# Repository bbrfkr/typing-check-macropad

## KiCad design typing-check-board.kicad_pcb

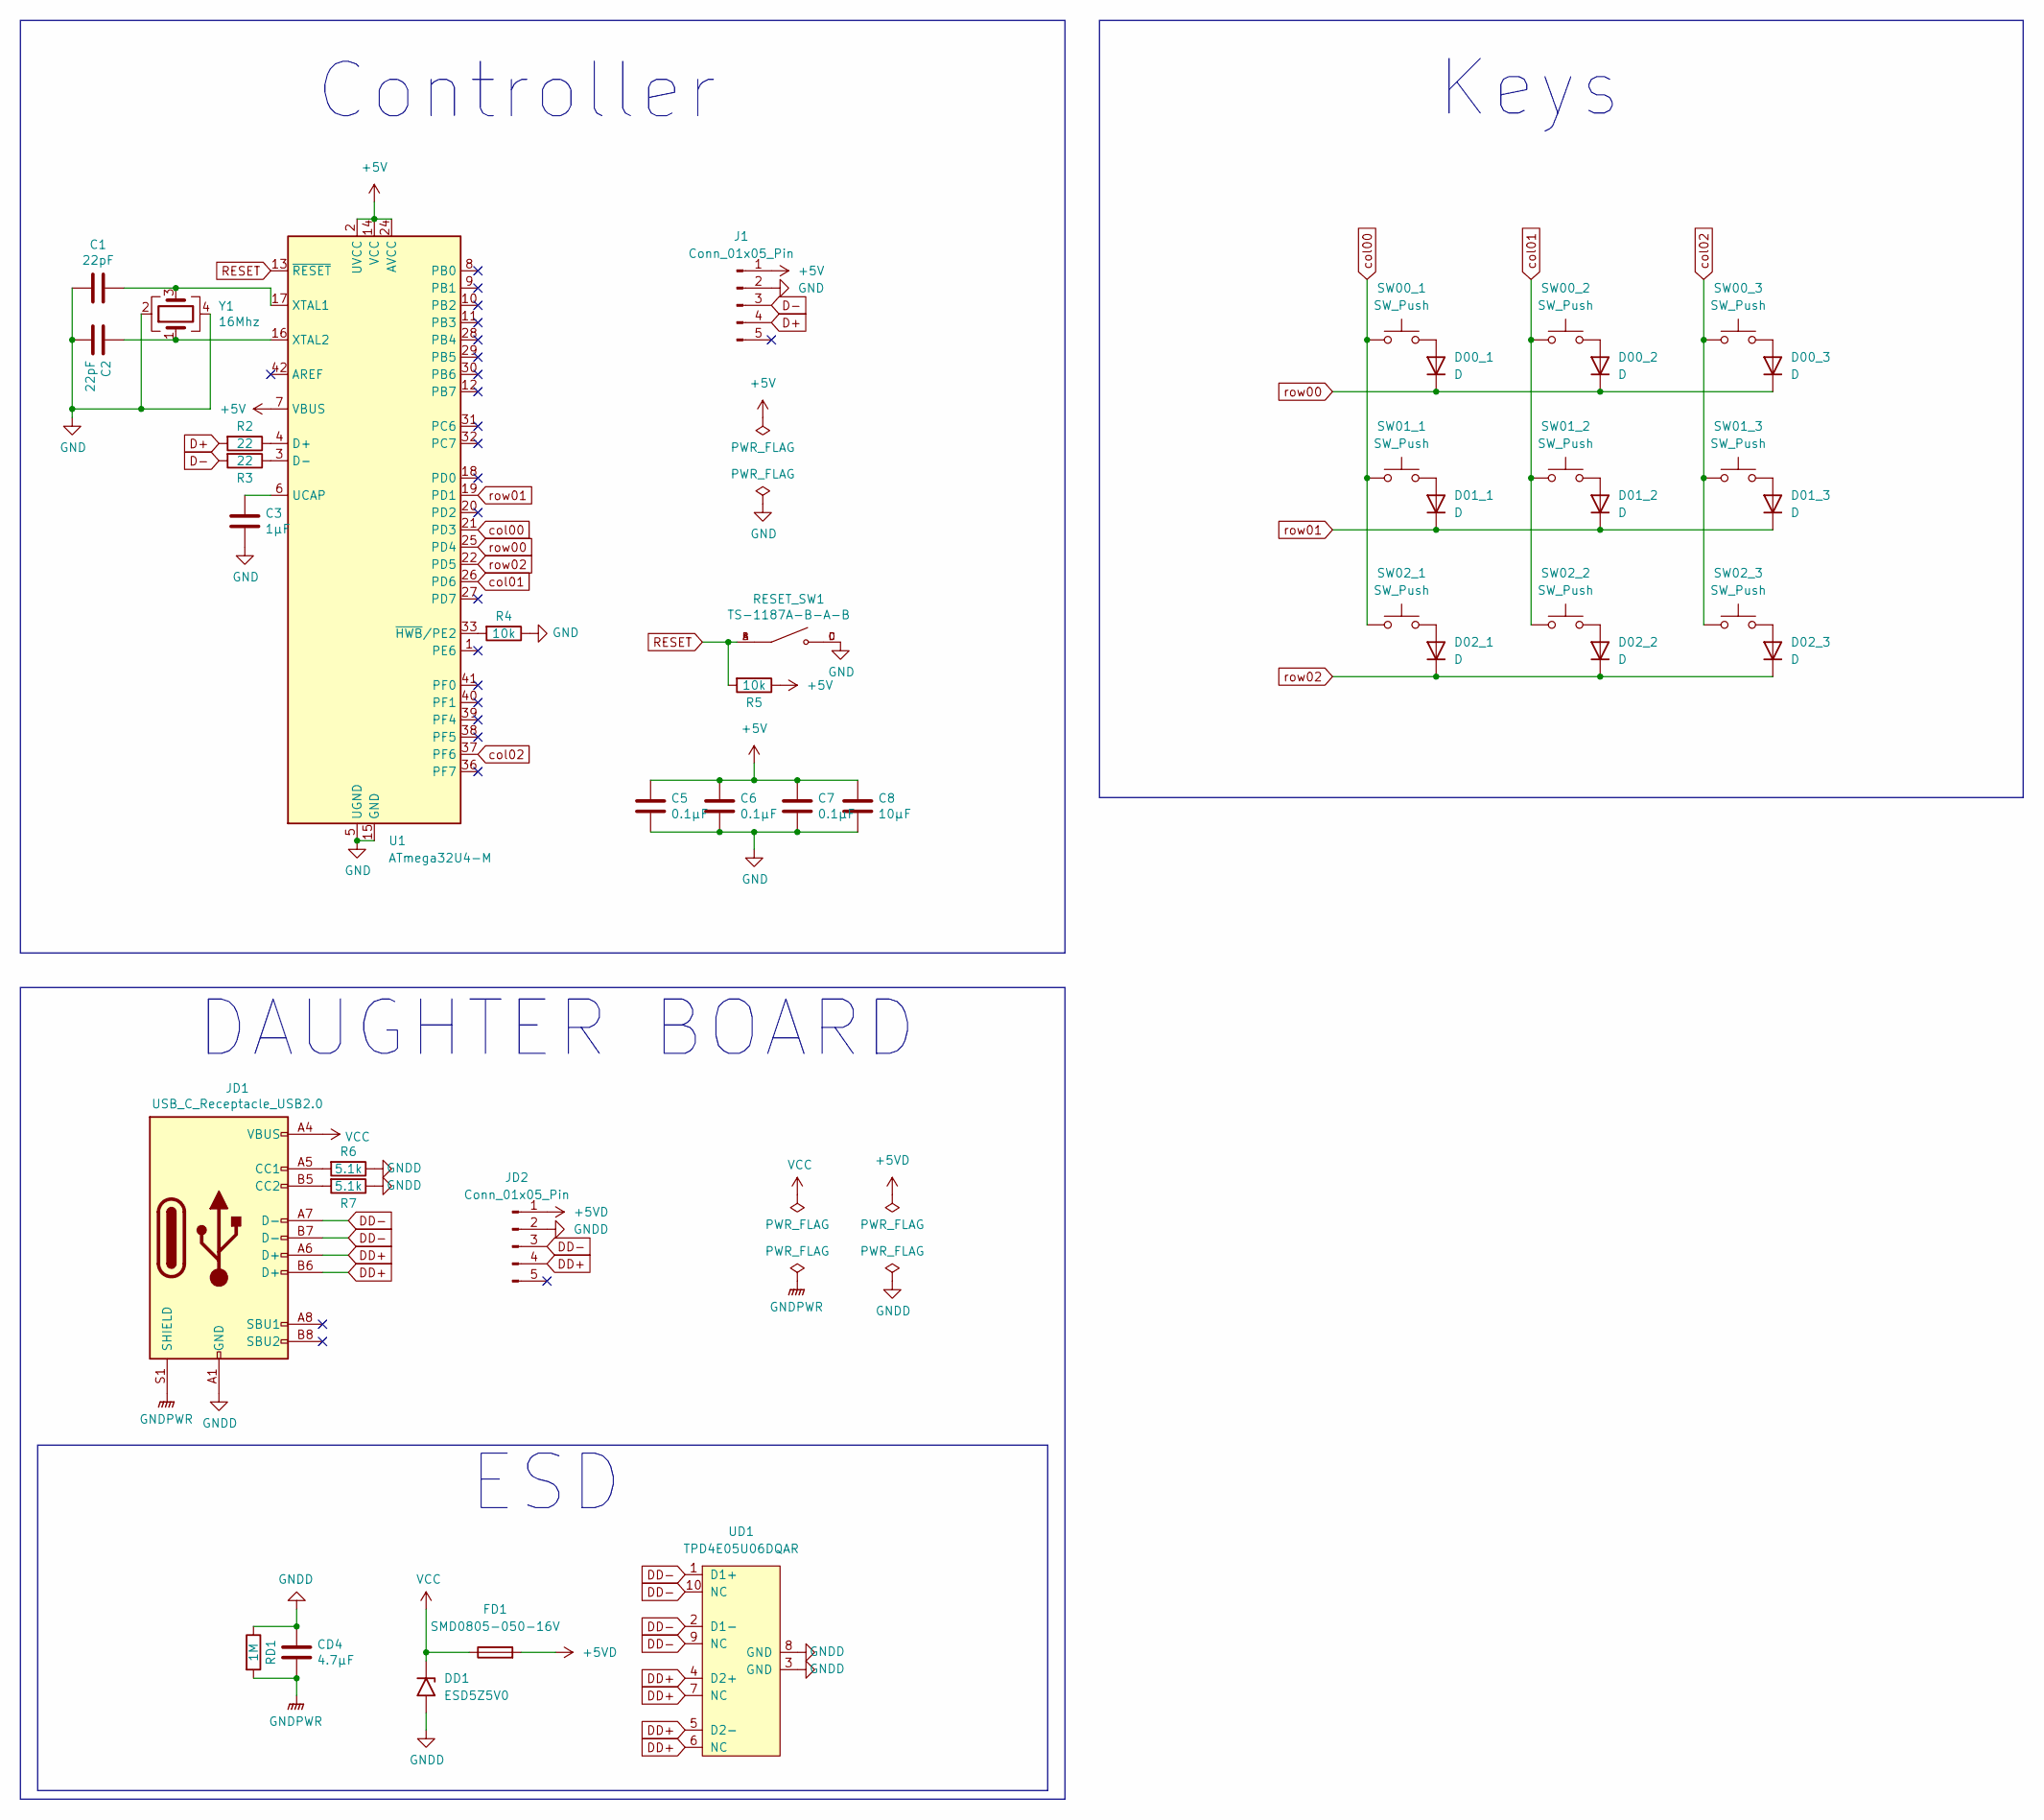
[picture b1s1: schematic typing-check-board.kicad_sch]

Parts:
C1, C2: 22pF; C_1206_3216Metric; LCSC C107174
C3: 1μF; C_1206_3216Metric; LCSC C1848
C5, C6, C7: 0.1μF; C_1206_3216Metric; LCSC C24497
C8: 10μF; C_1206_3216Metric; LCSC C13585
CD4: 4.7μF; C_1206_3216Metric; LCSC C29823
D00_1, D00_2, D00_3, D01_1, D01_2, D01_3, D02_1, D02_2, D02_3: D; D_SOD-123-Pretty; LCSC C81598
DD1: ESD5Z5V0; D_SOD-523; Manufacturer Part Number ESD5Z5V0; LCSC C502546
FD1: SMD0805-050-16V; Fuse_1206_3216Metric; Manufacturer Part Number SMD0805-050-16V; LCSC C2833485
J1: Conn_01x05_Pin; JST_PH_S5B-PH-K_1x05_P2.00mm_Horizontal
JD1: USB_C_Receptacle_USB2.0; USB_C_Receptacle_HRO_TYPE-C-31-M-12; LCSC C165948
JD2: Conn_01x05_Pin; JST_PH_S5B-PH-K_1x05_P2.00mm_Horizontal
R2, R3: 22; R_1206_3216Metric; LCSC C17958
R4, R5: 10k; R_1206_3216Metric; LCSC C17928
R6, R7: 5.1k; R_1206_3216Metric; LCSC C964991
RD1: 1M; R_1206_3216Metric; LCSC C2759631
RESET_SW1: TS-1187A-B-A-B; SW_TS-1187A-B-A-B; PARTREV A0; LCSC C318884
SW00_1, SW00_2, SW00_3, SW01_1, SW01_2, SW01_3, SW02_1, SW02_2, SW02_3: SW_Push; MXOnly-1U-Hotswap; LCSC C5156480
U1: ATmega32U4-M; QFN-44-1EP_7x7mm_P0.5mm_EP5.2x5.2mm; LCSC C112161
UD1: TPD4E05U06DQAR; USON-10_L2.5-W1.0-P0.50-BL; LCSC C2836386
Y1: 16Mhz; OSC-SMD_4P-L3.2-W2.5-BL; LCSC C13738

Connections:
+5V: C5.1, C6.1, C7.1, C8.1, J1.1, R5.1, U1.2 (UVCC), U1.7 (VBUS), U1.14 (VCC), U1.24 (AVCC), U1.34 (VCC), U1.44 (AVCC)
+5VD: FD1.2, JD2.1
D+: J1.4, R2.2
D-: J1.3, R3.2
DD+: JD1.A6 (D+), JD1.B6 (D+), JD2.4, UD1.4 (D2+), UD1.5 (D2-), UD1.6 (NC), UD1.7 (NC)
DD-: JD1.A7 (D-), JD1.B7 (D-), JD2.3, UD1.1 (D1+), UD1.2 (D1-), UD1.9 (NC), UD1.10 (NC)
GND: C1.1, C2.2, C3.2, C5.2, C6.2, C7.2, C8.2, J1.2, R4.1, RESET_SW1.C, RESET_SW1.D, U1.5 (UGND), U1.15 (GND), U1.23 (GND), U1.35 (GND), U1.43 (GND), U1.45 (GND), Y1.2, Y1.4
GNDD: CD4.1, DD1.2 (A2), JD1.A1 (GND), JD1.A12 (GND), JD1.B1 (GND), JD1.B12 (GND), JD2.2, R6.1, R7.1, RD1.1, UD1.3 (GND), UD1.8 (GND)
GNDPWR: CD4.2, JD1.S1 (SHIELD), RD1.2
unnamed: D00_1.2 (A), SW00_1.2
unnamed: D00_2.2 (A), SW00_2.2
unnamed: D00_3.2 (A), SW00_3.2
unnamed: D01_1.2 (A), SW01_1.2
unnamed: D01_2.2 (A), SW01_2.2
unnamed: D01_3.2 (A), SW01_3.2
unnamed: D02_1.2 (A), SW02_1.2
unnamed: D02_2.2 (A), SW02_2.2
unnamed: D02_3.2 (A), SW02_3.2
unnamed: JD1.A5 (CC1), R6.2
unnamed: JD1.B5 (CC2), R7.2
unnamed: R2.1, U1.4 (D+)
unnamed: R3.1, U1.3 (D-)
unnamed: C3.1, U1.6 (UCAP)
unnamed: C1.2, U1.17 (XTAL1), Y1.3
unnamed: C2.1, U1.16 (XTAL2), Y1.1
unnamed: R4.2, U1.33 (~HWB/PE2)
RESET: R5.2, RESET_SW1.A, RESET_SW1.B, U1.13 (~RESET)
VCC: DD1.1 (A1), FD1.1, JD1.A4 (VBUS), JD1.A9 (VBUS), JD1.B4 (VBUS), JD1.B9 (VBUS)
col00: SW00_1.1, SW01_1.1, SW02_1.1, U1.21 (PD3)
col01: SW00_2.1, SW01_2.1, SW02_2.1, U1.26 (PD6)
col02: SW00_3.1, SW01_3.1, SW02_3.1, U1.37 (PF6)
row00: D00_1.1 (K), D00_2.1 (K), D00_3.1 (K), U1.25 (PD4)
row01: D01_1.1 (K), D01_2.1 (K), D01_3.1 (K), U1.19 (PD1)
row02: D02_1.1 (K), D02_2.1 (K), D02_3.1 (K), U1.22 (PD5)

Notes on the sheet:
Keys
DAUGHTER BOARD
ESD
Controller

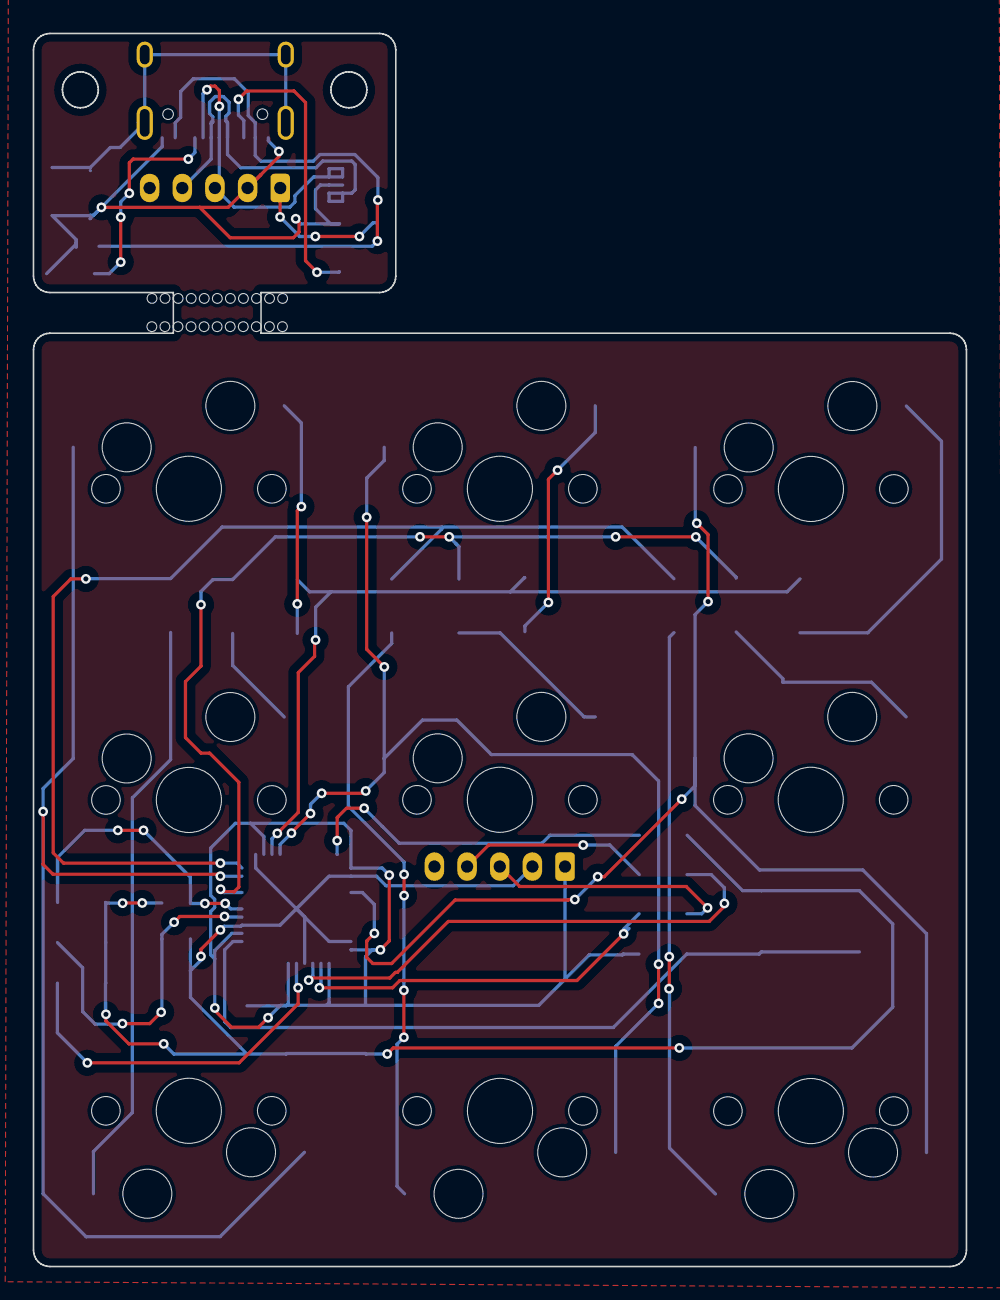
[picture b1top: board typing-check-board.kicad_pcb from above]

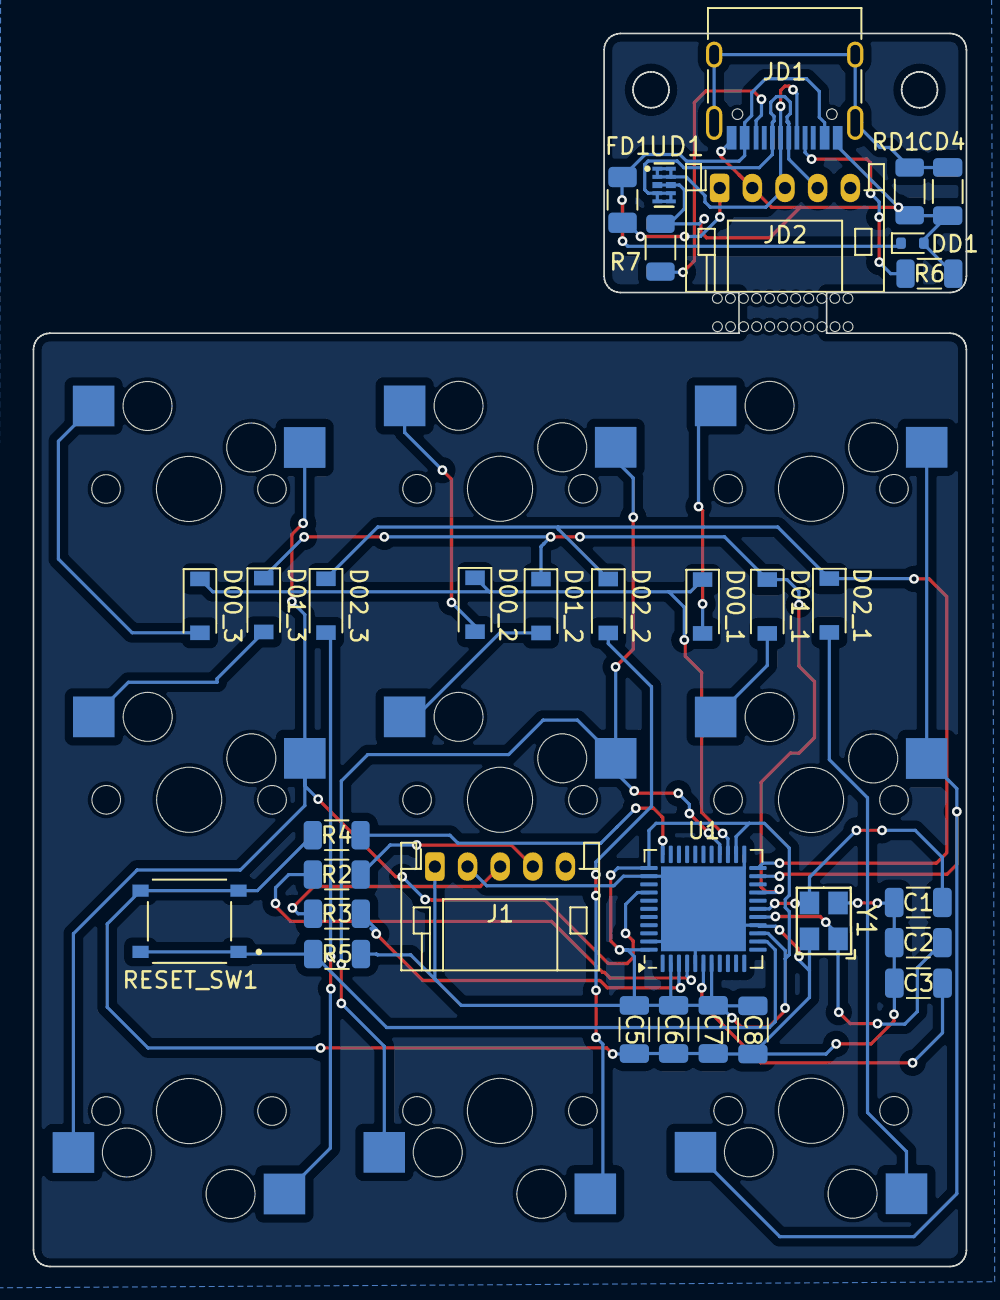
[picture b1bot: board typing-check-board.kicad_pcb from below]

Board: 2 copper layers, 57.1 x 75.5 mm, 44 parts (33 on the bottom side), 34 nets.

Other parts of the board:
bite01, bite02: bites; mousebites

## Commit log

2024-10-13 init
2024-10-14 pcb and plate
